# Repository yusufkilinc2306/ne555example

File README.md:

# ne555example
Simple circuits drawn in KiCAD using NE555 IC.

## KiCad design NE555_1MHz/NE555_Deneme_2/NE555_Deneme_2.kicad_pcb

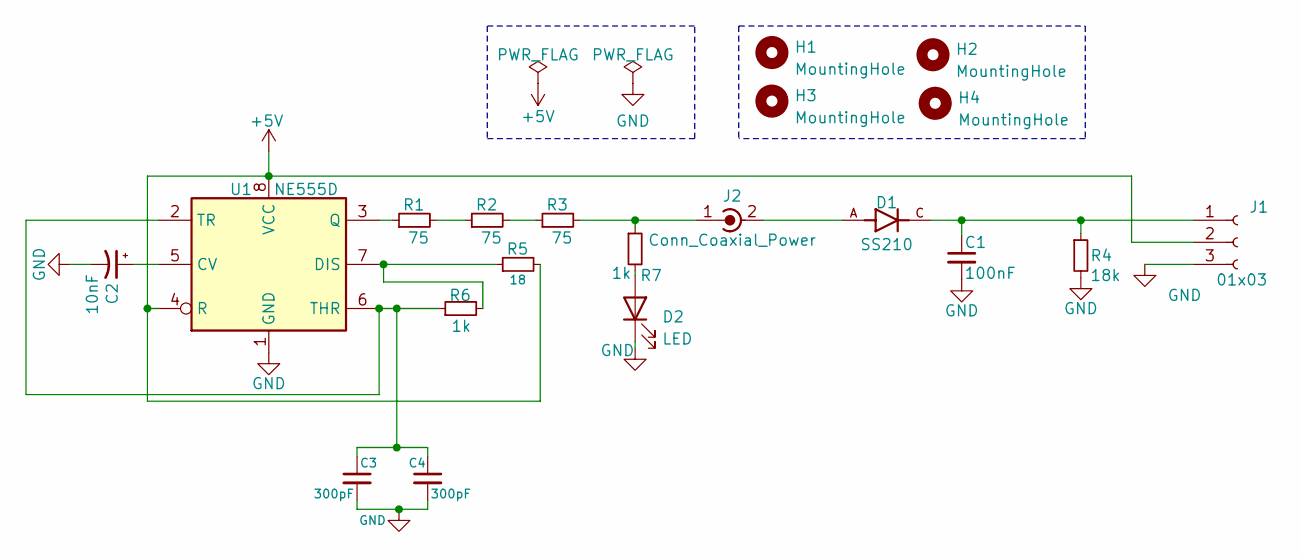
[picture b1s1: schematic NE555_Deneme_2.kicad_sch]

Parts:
C1: 100nF; C_0805_2012Metric_Pad1.18x1.45mm_HandSolder
C2: 10nF; C_0603_1608Metric_Pad1.08x0.95mm_HandSolder
C3, C4: 300pF; C_0603_1608Metric_Pad1.08x0.95mm_HandSolder
D1: SS210; DIOM4336X265N; PARTREV K2102
D2: LED; LED_1206_3216Metric_Pad1.42x1.75mm_HandSolder
H1, H2, H3, H4: MountingHole; MountingHole_2.5mm
J1: 01x03; PinSocket_1x03_P2.54mm_Vertical
J2: Conn_Coaxial_Power; BNC_Amphenol_B6252HB-NPP3G-50_Horizontal
R1, R2, R3: 75; R_0805_2012Metric_Pad1.20x1.40mm_HandSolder
R4: 18k; R_0805_2012Metric_Pad1.20x1.40mm_HandSolder
R5: 18; R_0805_2012Metric_Pad1.20x1.40mm_HandSolder
R6, R7: 1k; R_0603_1608Metric_Pad0.98x0.95mm_HandSolder
U1: NE555D; SOIC-8_3.9x4.9mm_P1.27mm

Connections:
+5V: J1.2, R5.2, U1.4 (R), U1.8 (VCC)
GND: C1.2, C2.2, C3.2, C4.2, D2.1 (K), J1.3, R4.2, U1.1 (GND)
unnamed: D2.2 (A), R7.2
unnamed: C1.1, D1.C, J1.1, R4.1
unnamed: D1.A, J2.2 (Ext)
unnamed: J2.1 (In), R3.2, R7.1
unnamed: R1.2, R2.1
unnamed: R2.2, R3.1
unnamed: C2.1, U1.5 (CV)
unnamed: R5.1, R6.2, U1.7 (DIS)
unnamed: R1.1, U1.3 (Q)
unnamed: C3.1, C4.1, R6.1, U1.2 (TR), U1.6 (THR)

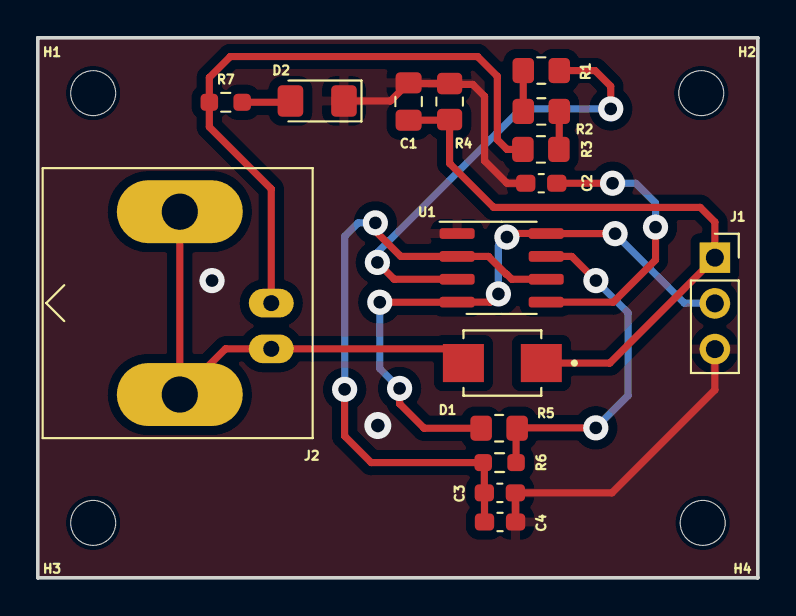
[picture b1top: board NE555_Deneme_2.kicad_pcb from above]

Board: 2 copper layers, 40.0 x 30.0 mm, 20 parts (0 on the bottom side), 12 nets.
